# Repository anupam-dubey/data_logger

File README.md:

##  Data Logger with SD card and CSV Export    

#### Project reads data from 9 DS18b20 sensors   
#### alongwith 3 DHT11 sensor for 12 temperature readouts   
### HARDWARE   
Arduino nano ds3231 rtc module sd card module
Arduino ide is used with 16gb fat32 sd card  
project completed on 20/3/2020

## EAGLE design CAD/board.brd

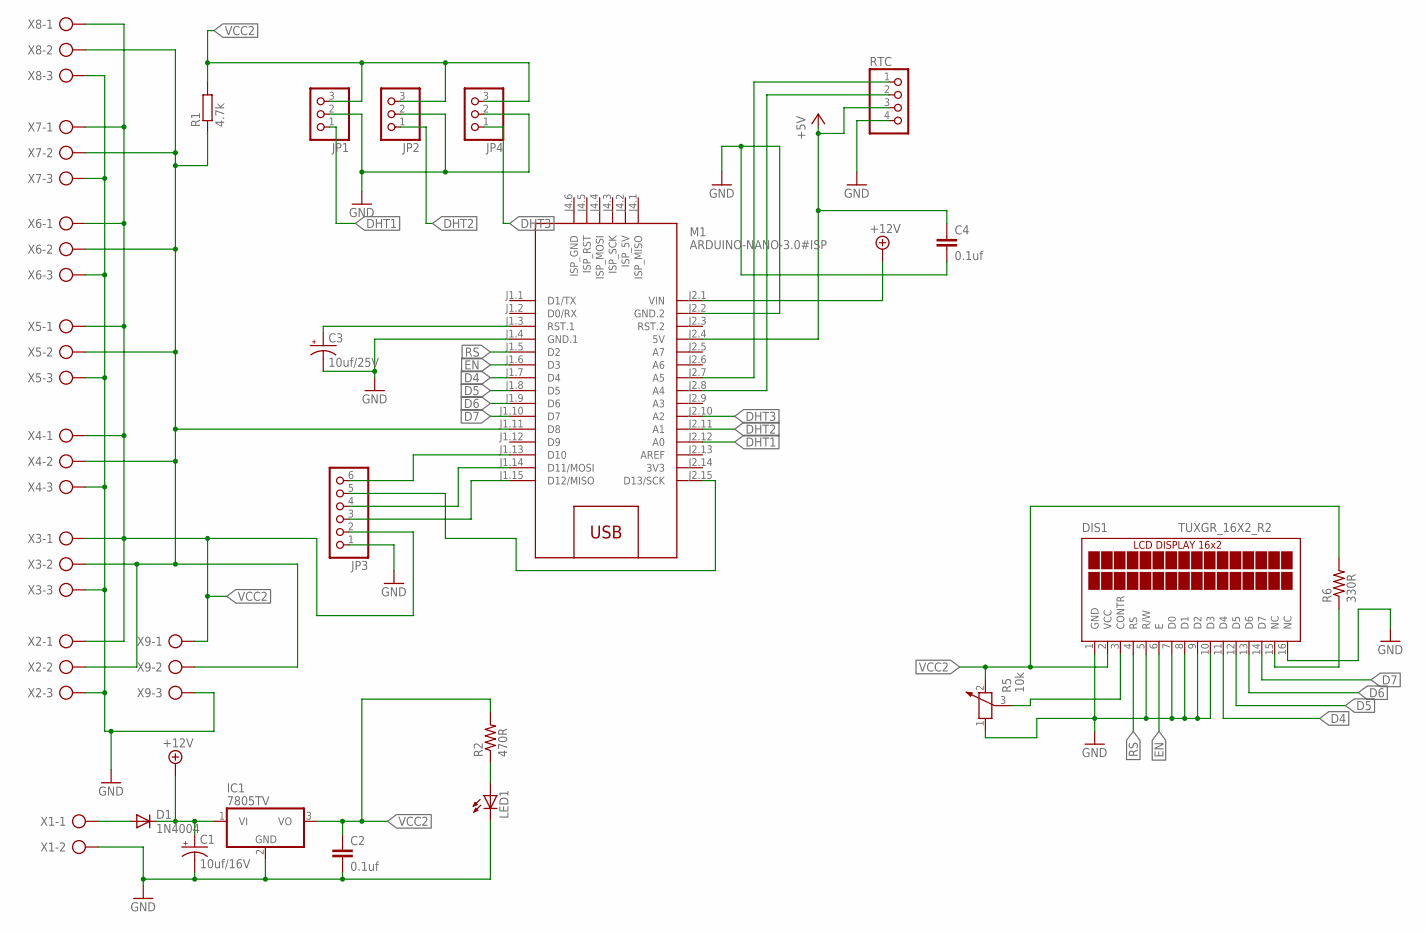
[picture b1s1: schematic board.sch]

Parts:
C1: 10uf/16V; E2,5-5
C2, C4: 0.1uf; C050-035X075
C3: 10uf/25V; E2,5-5
D1: 1N4004; DO41-10
DIS1: TUXGR_16X2_R2
IC1: 7805TV; TO220V
JP1, JP2, JP4: PINHD-1X3; 1X03
JP3: PINHD-1X6; 1X06
LED1: LED3MM
M1: ARDUINO-NANO-3.0#ISP
R1: 4.7k; 0207/10
R2: 470R; 0207/10@1
R5: 10k; PT-10
R6: 330R; 0207/10@1
RTC: PINHD-1X4; 1X04
X1: AK500/2
X2, X3, X4, X5, X6, X7, X8, X9: AK500/3

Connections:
3V3: M1.J2.14 (3V3)
+5V: C4.1, M1.J2.4 (5V), RTC.3
+12V: C1.+, D1.C, IC1.1 (VI), M1.J2.1 (VIN)
D4: DIS1.11 (D4), M1.J1.7 (D4)
D5: DIS1.12 (D5), M1.J1.8 (D5)
D6: DIS1.13 (D6), M1.J1.9 (D6)
D7: DIS1.14 (D7), M1.J1.10 (D7)
DHT1: JP1.1, M1.J2.12 (A0)
DHT2: JP2.1, M1.J2.11 (A1)
DHT3: JP4.1, M1.J2.10 (A2)
EN: DIS1.6 (E), M1.J1.6 (D3)
GND: C1.-, C2.2, C3.-, C4.2, DIS1.1 (GND), DIS1.5 (R/W), DIS1.7 (D0), DIS1.8 (D1), DIS1.9 (D2), DIS1.10 (D3), DIS1.16 (NC), IC1.2 (GND), JP1.2, JP2.2, JP3.1, JP4.2, LED1.K (C), M1.J1.4 (GND.1), M1.J2.2 (GND.2), R5.1, RTC.4, X1.2, X2.3, X3.3, X4.3, X5.3, X6.3, X7.3, X8.3, X9.3
unnamed: D1.A, X1.1
unnamed: C3.+, M1.J1.3 (RST.1)
unnamed: JP1.3, JP2.3, JP4.3, R1.2
unnamed: M1.J2.7 (A5), RTC.1
unnamed: M1.J2.8 (A4), RTC.2
unnamed: M1.J1.11 (D8), R1.1, X2.2, X3.2, X4.2, X5.2, X6.2, X7.2, X8.2, X9.2
unnamed: DIS1.3 (CONTR), R5.3
unnamed: DIS1.15 (NC), R6.1
unnamed: JP3.3, M1.J1.15 (D12/MISO)
unnamed: JP3.4, M1.J1.14 (D11/MOSI)
unnamed: JP3.5, M1.J2.15 (D13/SCK)
unnamed: JP3.6, M1.J1.13 (D10)
unnamed: LED1.A, R2.1
RS: DIS1.4 (RS), M1.J1.5 (D2)
VCC2: C2.1, DIS1.2 (VCC), IC1.3 (VO), JP3.2, R2.2, R5.2, R6.2, X2.1, X3.1, X4.1, X5.1, X6.1, X7.1, X8.1, X9.1

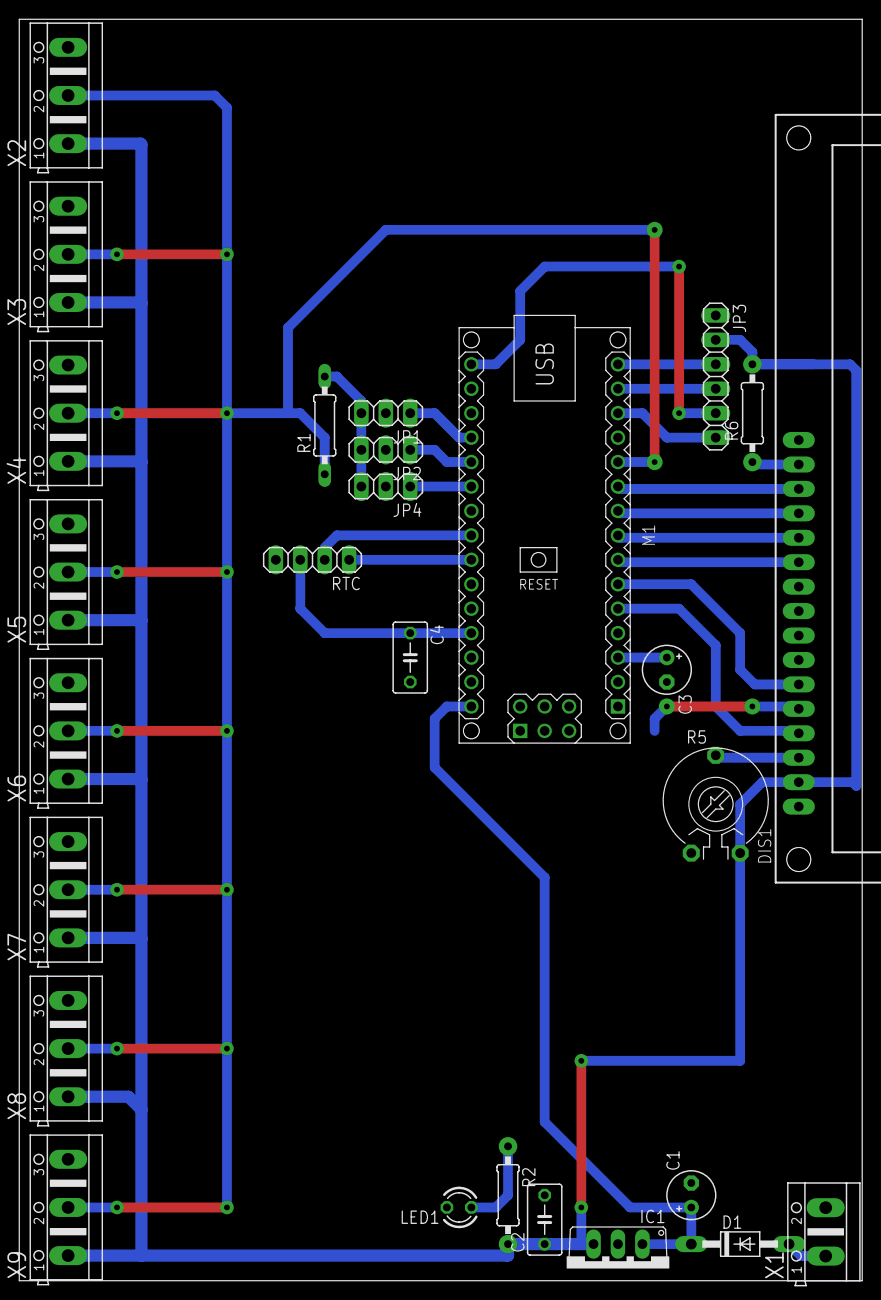
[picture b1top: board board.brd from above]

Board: 2 copper layers, 87.6 x 131.1 mm, 27 parts (0 on the bottom side), 26 nets.

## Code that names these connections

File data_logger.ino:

// just for ketan
#include <SPI.h>
#include <SD.h>
#include <DS3231.h>
#include <LiquidCrystal.h> // includes the LiquidCrystal Library 
#include <dht.h>
#include <OneWire.h>
#include <DallasTemperature.h>

#define dht1_pin A0
#define dht2_pin A1
#define dht3_pin A2

// Data wire is plugged into digital pin 2 on the Arduino
#define ONE_WIRE_BUS 8
int deviceCount = 0;
unsigned long interval=60000; // the time we need to wait
unsigned long previousMillis=0; // millis() returns an unsigned long.
// Setup a oneWire instance to communicate with any OneWire device
OneWire oneWire(ONE_WIRE_BUS);  

// Pass oneWire reference to DallasTemperature library
DallasTemperature sensors(&oneWire);

dht DHT1;
dht DHT2;
dht DHT3;
DS3231  rtc(SDA, SCL);
long id = 1;              //Store the id# of our reading
const int chipSelect = 10;
float t1,t2,t3,h1,h2,h3;
float temp[9];
LiquidCrystal lcd(2, 3, 4, 5, 6, 7); // Creates an LC object. Parameters: (rs, enable, d4, d5, d6, d7) 
void read_all_dht(void);
void read_all_temp(void);
void compress_save(void);
void setup() { 
  Serial.begin(115200);
 rtc.begin(); // Initialize the rtc object
 sensors.begin(); // Start up the library
 lcd.begin(16,2); // Initializes the interface to the LCD screen, and specifies the dimensions (width and height) of the display } 
//  rtc.setDOW(FRIDAY);     // Set Day-of-Week to SUNDAY
//  rtc.setTime(12, 58, 0);     // Set the time to 12:00:00 (24hr format)
//  rtc.setDate(20, 3, 2020);   // Set the date to January 1st, 2014
  pinMode(10, OUTPUT);
  delay(100);
   // see if the card is present and can be initialized:
  if (!SD.begin(chipSelect)) {
   // Serial.println("Card failed, or not present");
     lcd.setCursor(0,1);
     lcd.print("Card Fail");delay(1350);
    // don't do anything more:
    return;
  }
  lcd.setCursor(0,1);
  lcd.print("Card Success");delay(1350);
  //Write Log.csv File Header
  File logFile = SD.open("LOG.csv", FILE_WRITE);
  if (logFile)
  {
    logFile.println(", , , , , , , , , , , , , , , , ,"); //Just a leading blank line, incase there was previous data
    logFile.println("ID, Date, Time, T1, H1, T2, H2, T3, H3, T4, T5, T6, T7, T8, T9, T10, T11, T12");
    logFile.close();
  }
  read_all_dht();
  lcd.clear();
  delay(1000);
  lcd.print(t1,1);
  lcd.print(" ");
  lcd.print(t2,1);
  lcd.print(" ");
  lcd.print(t3,1);
  lcd.print(" ");
  lcd.setCursor(0,1);
  lcd.print(h1,1);
  lcd.print(" ");
  lcd.print(h2,1);
  lcd.print(" ");
  lcd.print(h3,1);
  lcd.print(" ");
  delay(2000);
  lcd.clear();
  deviceCount = sensors.getDeviceCount();
  lcd.print(deviceCount, DEC);
  lcd.setCursor(0,1);
  lcd.print("sensors. Found");
  delay(2000);
  lcd.clear();
}
void loop() { 
 unsigned long currentMillis = millis(); // grab current time
 
 // check if "interval" time has passed (1000 milliseconds)
 if ((unsigned long)(currentMillis - previousMillis) >= interval) {
  
   read_all_dht();
   read_all_temp();
   compress_save();
   // save the "current" time
   previousMillis = millis();
 }
 lcd.setCursor(0,0);
 lcd.print("Time:  ");
 lcd.print(rtc.getTimeStr());
 
 lcd.setCursor(0,1);
 lcd.print("Date: ");
 lcd.print(rtc.getDateStr());
  delay(1000); 
}
void read_all_dht()
{
  DHT1.read11(dht1_pin);
  DHT2.read11(dht2_pin);
  DHT3.read11(dht3_pin);
  h1=DHT1.humidity;
  t1=DHT1.temperature;
  h2=DHT2.humidity;
  t2=DHT2.temperature;
  h3=DHT3.humidity;
  t3=DHT3.temperature;
}
void read_all_temp()
{
 sensors.requestTemperatures(); 
  
  // Display temperature from each sensor
  lcd.clear();
  for (int i = 0;  i < deviceCount;  i++)
  { lcd.setCursor(0,0);
    lcd.print(i+1);
    lcd.print(" ");
    temp[i] = sensors.getTempCByIndex(i);
    lcd.print(temp[i],1);
    delay(500);
  }  
}
void compress_save()
{
   //Open a file to write to
  //Only one file can be open at a time
  String dataString = String(id) + ", " + rtc.getDateStr()+", " + rtc.getTimeStr() ;
  dataString += ", " + String(t1) + ", " + String(h1);
  dataString += ", " + String(t2) + ", " + String(h2);
  dataString += ", " + String(t3) + ", " + String(h3);
  dataString += ", " + String(temp[0]) + ", " + String(temp[1]);
  dataString += ", " + String(temp[2]) + ", " + String(temp[3]);
  dataString += ", " + String(temp[4]) + ", " + String(temp[5]);
  dataString += ", " + String(temp[6]) + ", " + String(temp[7]);
  dataString += ", " + String(temp[8]);
  Serial.println(dataString);
  File logFile = SD.open("LOG.csv", FILE_WRITE);
  if(logFile)
  {
    logFile.println(dataString);
    logFile.close();
  //  Serial.println(dataString);
  }
}

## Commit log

2022-07-26 second

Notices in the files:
parts and their libraries:
diy-modules: Released under the Creative Commons Attribution 4.0 International License: http://creativecommons.org/licenses/by/4.0
SparkFun-Aesthetics: Licensing: Creative Commons ShareAlike 4.0 International - https://creativecommons.org/licenses/by-sa/4.0
